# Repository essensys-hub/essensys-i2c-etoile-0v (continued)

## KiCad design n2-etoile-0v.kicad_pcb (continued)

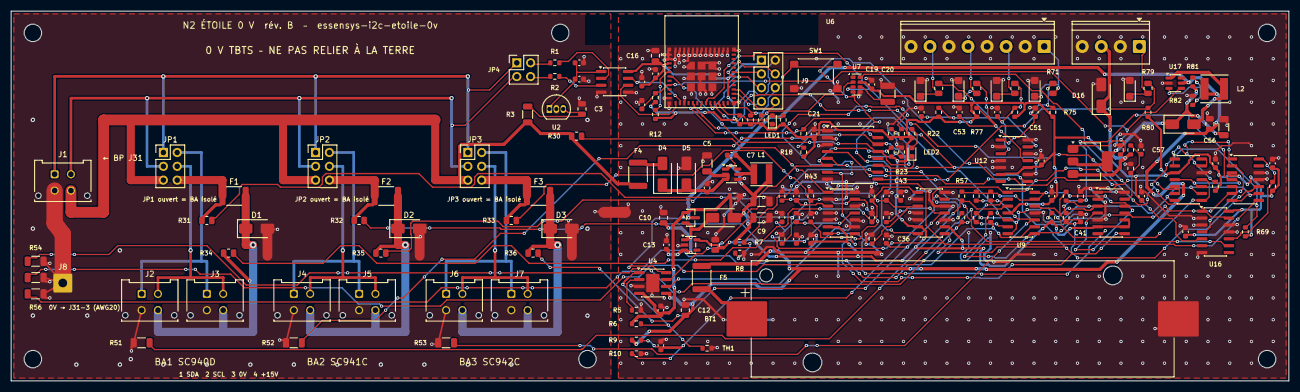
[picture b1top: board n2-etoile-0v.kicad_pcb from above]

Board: 2 copper layers, 235.0 x 68.0 mm, 181 parts (0 on the bottom side), 98 nets.

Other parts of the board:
H1, H2, H3, H4, H5, H6: M3 isolé; MountingHole_3.2mm_M3

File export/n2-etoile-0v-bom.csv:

"Repère","Valeur","Empreinte","Fabricant","Référence","Tolérance","Qté"
"BT1","LiFePO4 18650 3,2 V 1,5 Ah","Battery:BatteryHolder_Keystone_1042_1x18650","Keystone","1042 (porte-pile 18650) + cellule IFR18650 1500 mAh","","1"
"C1,C2,C7,C17,C19,C21,C40-C48","100n","Capacitor_SMD:C_0603_1608Metric","","","","15"
"C3","1u 50V","Capacitor_SMD:C_0805_2012Metric","","","","1"
"C4","2u2","Capacitor_SMD:C_0603_1608Metric","","","","1"
"C5","10u 35V","Capacitor_SMD:C_1206_3216Metric","","","","1"
"C6","100n 50V","Capacitor_SMD:C_0603_1608Metric","","","","1"
"C8,C9","22u 10V","Capacitor_SMD:C_1206_3216Metric","","","","2"
"C10,C12,C14,C16,C56","10u","Capacitor_SMD:C_0805_2012Metric","","","","5"
"C11,C13,C18","1u","Capacitor_SMD:C_0603_1608Metric","","","","3"
"C15,C31-C36,C57","1n","Capacitor_SMD:C_0603_1608Metric","","","","8"
"C20","11m 3,3V","Capacitor_SMD:C_1210_3225Metric","Seiko","CPH3225A (supercondensateur, chargé par le trickle charger du RV-3028)","","1"
"C30","100p","Capacitor_SMD:C_0603_1608Metric","","","","1"
"C51-C54","10n","Capacitor_SMD:C_0603_1608Metric","","","","4"
"C55","22u 25V","Capacitor_SMD:C_1206_3216Metric","","","","1"
"D1-D3,D5,D16","SMAJ16A","Diode_SMD:D_SMA","Littelfuse","SMAJ16A","","5"
"D4,D6,D7","SS14","Diode_SMD:D_SMA","","","","3"
"D11-D15","SMF5V0A","Diode_SMD:D_SMF","Littelfuse","SMF5.0A","","5"
"F1-F3","PTC >=30 V 1812","Fuse:Fuse_1812_4532Metric","Littelfuse","1812L050/30MR (à confirmer : Ihold@50°C >= 1,5 x I BA_ALIM)","","3"
"F4","PTC 0,2 A 1812","Fuse:Fuse_1812_4532Metric","Bourns","MF-MSMF020-2 (Ihold 0,2 A, 30 V, à confirmer)","","1"
"F5","PTC 1,5 A 1812","Fuse:Fuse_1812_4532Metric","Littelfuse","1812L150/12MR (à confirmer)","","1"
"J1","BP J31 (WR-MPC3 2x2)","Connector_Molex:Molex_Micro-Fit_3.0_43045-0412_2x02_P3.00mm_Vertical","Würth Elektronik","66200421122 (WR-MPC3 2x2, vertical, THT)","","1"
"J2","BA1 J1 (WR-MPC3 2x2)","Connector_Molex:Molex_Micro-Fit_3.0_43045-0412_2x02_P3.00mm_Vertical","Würth Elektronik","66200421122 (WR-MPC3 2x2, vertical, THT)","","1"
"J3","BA1 J2 (WR-MPC3 2x2)","Connector_Molex:Molex_Micro-Fit_3.0_43045-0412_2x02_P3.00mm_Vertical","Würth Elektronik","66200421122 (WR-MPC3 2x2, vertical, THT)","","1"
"J4","BA2 J1 (WR-MPC3 2x2)","Connector_Molex:Molex_Micro-Fit_3.0_43045-0412_2x02_P3.00mm_Vertical","Würth Elektronik","66200421122 (WR-MPC3 2x2, vertical, THT)","","1"
"J5","BA2 J2 (WR-MPC3 2x2)","Connector_Molex:Molex_Micro-Fit_3.0_43045-0412_2x02_P3.00mm_Vertical","Würth Elektronik","66200421122 (WR-MPC3 2x2, vertical, THT)","","1"
"J6","BA3 J1 (WR-MPC3 2x2)","Connector_Molex:Molex_Micro-Fit_3.0_43045-0412_2x02_P3.00mm_Vertical","Würth Elektronik","66200421122 (WR-MPC3 2x2, vertical, THT)","","1"
"J7","BA3 J2 (WR-MPC3 2x2)","Connector_Molex:Molex_Micro-Fit_3.0_43045-0412_2x02_P3.00mm_Vertical","Würth Elektronik","66200421122 (WR-MPC3 2x2, vertical, THT)","","1"
"J9","Débogage UART/USB","Connector_PinHeader_2.54mm:PinHeader_2x04_P2.54mm_Vertical","","","","1"
"J10","Boucles Z1-Z4","TerminalBlock_Phoenix:TerminalBlock_Phoenix_PT-1,5-8-3.5-H_1x08_P3.50mm_Horizontal","Phoenix Contact","1984688 (PT 1,5/8-3,5-H)","","1"
"J11","Clé ARM / sirène 12 V","TerminalBlock_Phoenix:TerminalBlock_Phoenix_PT-1,5-4-3.5-H_1x04_P3.50mm_Horizontal","Phoenix Contact","1984633 (PT 1,5/4-3,5-H)","","1"
"JP1","Cavalier port BA1 (3 shunts)","Connector_PinHeader_2.54mm:PinHeader_2x03_P2.54mm_Vertical","","","","1"
"JP2","Cavalier port BA2 (3 shunts)","Connector_PinHeader_2.54mm:PinHeader_2x03_P2.54mm_Vertical","","","","1"
"JP3","Cavalier port BA3 (3 shunts)","Connector_PinHeader_2.54mm:PinHeader_2x03_P2.54mm_Vertical","","","","1"
"JP4","Cavalier d'écoute (2 shunts)","Connector_PinHeader_2.54mm:PinHeader_2x02_P2.54mm_Vertical","","","","1"
"L1","4,7u","Inductor_SMD:L_Taiyo-Yuden_NR-40xx","Taiyo Yuden","NR4018T4R7M","","1"
"L2","22u","Inductor_SMD:L_Taiyo-Yuden_NR-50xx","Taiyo Yuden","NR5040T220M","","1"
"LED1","LED verte (état)","LED_SMD:LED_0603_1608Metric","","","","1"
"LED2","LED rouge (alarme)","LED_SMD:LED_0603_1608Metric","","","","1"
"Q1","AO3401A","Package_TO_SOT_SMD:SOT-23","","","","1"
"R1,R2,R16,R22","1k","Resistor_SMD:R_0603_1608Metric","","","","4"
"R3","100","Resistor_SMD:R_1206_3216Metric","","","","1"
"R4,R83","100k","Resistor_SMD:R_0603_1608Metric","","","","2"
"R5","9k1","Resistor_SMD:R_0603_1608Metric","","","","1"
"R6","6k2","Resistor_SMD:R_0603_1608Metric","","","","1"
"R7,R11-R15,R19-R21,R23,R67-R69,R75-R78,R80,R82","10k","Resistor_SMD:R_0603_1608Metric","","","","19"
"R8","20k","Resistor_SMD:R_0603_1608Metric","","","","1"
"R9,R10,R84","100k","Resistor_SMD:R_0603_1608Metric","","","0,1 % 25 ppm/°C","3"
"R17,R18","4k7","Resistor_SMD:R_0603_1608Metric","","","","2"
"R30-R36","150k","Resistor_SMD:R_0805_2012Metric","","","0,1 % 25 ppm/°C","7"
"R40-R46,R85","10k","Resistor_SMD:R_0603_1608Metric","","","0,1 % 25 ppm/°C","8"
"R51-R56","100k","Resistor_SMD:R_1206_3216Metric","","","0,1 % 25 ppm/°C","6"
"R57-R62","24k9","Resistor_SMD:R_0603_1608Metric","","","0,1 % 25 ppm/°C","6"
"R63","20k5","Resistor_SMD:R_0603_1608Metric","","","0,1 % 25 ppm/°C","1"
"R64,R65","2k49","Resistor_SMD:R_0603_1608Metric","","","0,1 % 25 ppm/°C","2"
"R66","7k5","Resistor_SMD:R_0603_1608Metric","","","0,1 % 25 ppm/°C","1"
"R71-R74,R79","1k","Resistor_SMD:R_0805_2012Metric","","","","5"
"R81","191k","Resistor_SMD:R_0603_1608Metric","","","","1"
"SW1","BOOT / service","Button_Switch_SMD:SW_SPST_PTS645Sx43SMTR92","","","","1"
"TH1","CTN 10k B3435","Resistor_SMD:R_0603_1608Metric","Murata","NCP18XH103F03RB (au contact du porte-pile)","","1"
"U1","ISO7720D","Package_SO:SOIC-8_3.9x4.9mm_P1.27mm","Texas Instruments","ISO7720DR (2/0 canaux ; seconde source ADuM1200ARZ, même brochage)","","1"
"U2","LP2950-5.0","Package_TO_SOT_THT:TO-92_Inline","Texas Instruments","LP2950-50LPRE3 (VIN max 30 V)","","1"
"U3","AP63205WU","Package_TO_SOT_SMD:TSOT-23-6","Diodes Inc.","AP63205WU-7 (5 V fixe, 3,8-32 V)","","1"
"U4","CN3058E","Package_SO:SOIC-8-1EP_3.9x4.9mm_P1.27mm_EP2.41x3.3mm","Consonance","CN3058E (LiFePO4 3,6 V ; brochage à vérifier)","","1"
"U5","AP2112K-3.3","Package_TO_SOT_SMD:SOT-23-5","Diodes Inc.","AP2112K-3.3TRG1","","1"
"U6","ESP32-C3-MINI-1","RF_Module:ESP32-C6-MINI-1","Espressif","ESP32-C3-MINI-1-N4 (empreinte = motif MINI-1, identique au C6-MINI-1)","","1"
"U7","RV-3028-C7","Package_SON:MicroCrystal_C7_SON-8_1.5x3.2mm_P0.9mm","Micro Crystal","RV-3028-C7 32.768kHz 1ppm-TA-QC (I2C 0x52, EVI = horodatage du latch 0 V)","","1"
"U8","TCA9534DW","Package_SO:SOIC-16W_7.5x10.3mm_P1.27mm","Texas Instruments","TCA9534DWR (I2C 0x20)","","1"
"U9","TLV9064IDR","Package_SO:SOIC-14_3.9x8.7mm_P1.27mm","Texas Instruments","TLV9064IDR (10 MHz, RRIO)","","1"
"U10","MCP3428-E/SL","Package_SO:SOIC-14_3.9x8.7mm_P1.27mm","Microchip","MCP3428-E/SL (16 bits, réf. 2,048 V ; Adr0=GND Adr1=GND)","","1"
"U11","MCP3428-E/SL","Package_SO:SOIC-14_3.9x8.7mm_P1.27mm","Microchip","MCP3428-E/SL (16 bits, réf. 2,048 V ; Adr0=3V3 Adr1=GND)","","1"
"U12","MCP3428-E/SL","Package_SO:SOIC-14_3.9x8.7mm_P1.27mm","Microchip","MCP3428-E/SL (16 bits, réf. 2,048 V ; Adr0=GND Adr1=3V3)","","1"
"U13","MCP3428-E/SL","Package_SO:SOIC-14_3.9x8.7mm_P1.27mm","Microchip","MCP3428-E/SL (16 bits, réf. 2,048 V ; Adr0=3V3 Adr1=3V3)","","1"
"U14","LM339","Package_SO:SOIC-14_3.9x8.7mm_P1.27mm","Texas Instruments","LM339DR","","1"
"U15","LM339","Package_SO:SOIC-14_3.9x8.7mm_P1.27mm","Texas Instruments","LM339DR (U15D inutilisé)","","1"
"U16","74HC74","Package_SO:SOIC-14_3.9x8.7mm_P1.27mm","Nexperia","74HC74D","","1"
"U17","MT3608","Package_TO_SOT_SMD:SOT-23-6","Aerosemi","MT3608 (12 V depuis VBAT, actif seulement sirène en marche)","","1"
"U18","BTS4140N","Package_TO_SOT_SMD:SOT-223","Infineon","BTS4140N (high-side protégé : limitation de courant + coupure thermique)","","1"
